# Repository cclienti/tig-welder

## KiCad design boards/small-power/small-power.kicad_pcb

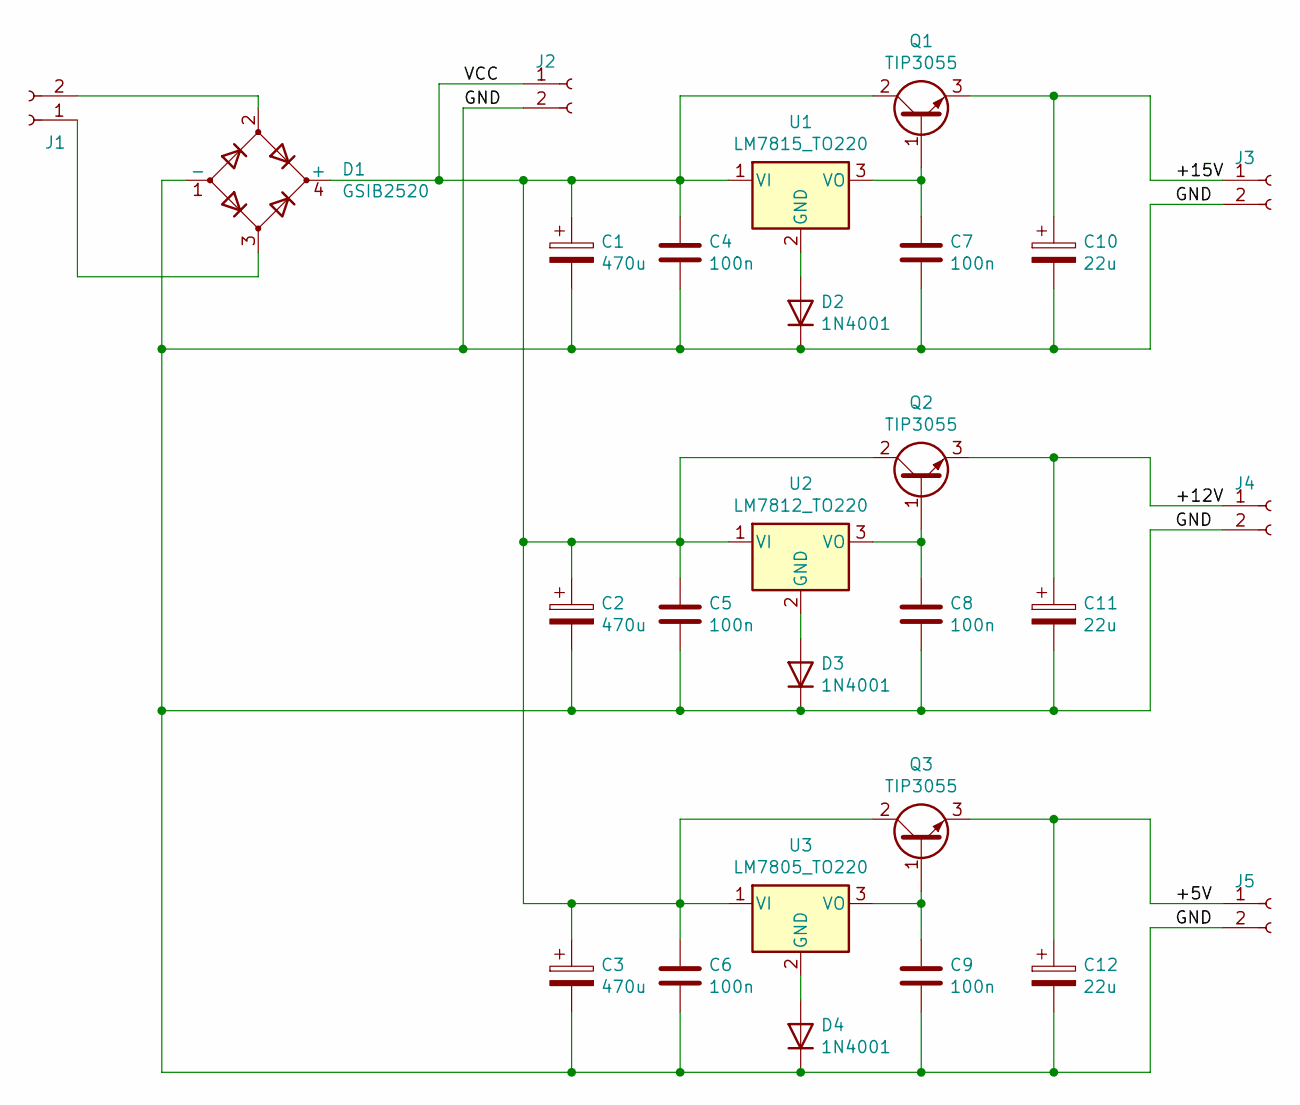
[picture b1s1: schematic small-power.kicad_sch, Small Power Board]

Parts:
C1, C2, C3: 470u; CP_Radial_D13.0mm_P5.00mm
C4, C5, C6, C7, C8, C9: 100n; C_Rect_L4.6mm_W2.0mm_P2.50mm_MKS02_FKP02
C10, C11, C12: 22u; CP_Radial_D5.0mm_P2.50mm
D1: GSIB2520; Diode_Bridge_32.0x5.6x17.0mm_P10.0mm_P7.5mm
D2, D3, D4: 1N4001; D_DO-41_SOD81_P10.16mm_Horizontal
J1, J2, J3, J4, J5: Conn_01x02_Female; PhoenixContact_MSTBVA_2,5_2-G-5,08_1x02_P5.08mm_Vertical
Q1, Q2, Q3: TIP3055; TO-218-3_Vertical
U1: LM7815_TO220; TO-220-3_Vertical
U2: LM7812_TO220; TO-220-3_Vertical
U3: LM7805_TO220; TO-220-3_Vertical

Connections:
/+5V: C12.1, J5.1, Q3.3 (E)
/+12V: C11.1, J4.1, Q2.3 (E)
/+15V: C10.1, J3.1, Q1.3 (E)
/GND: C1.2, C2.2, C3.2, C4.2, C5.2, C6.2, C7.2, C8.2, C9.2, C10.2, C11.2, C12.2, D1.1 (-), D2.1 (K), D3.1 (K), D4.1 (K), J2.2, J3.2, J4.2, J5.2
/VCC: C1.1, C2.1, C3.1, C4.1, C5.1, C6.1, D1.4 (+), J2.1, Q1.2 (C), Q2.2 (C), Q3.2 (C), U1.1 (VI), U2.1 (VI), U3.1 (VI)
unnamed: C7.1, Q1.1 (B), U1.3 (VO)
unnamed: C8.1, Q2.1 (B), U2.3 (VO)
unnamed: C9.1, Q3.1 (B), U3.3 (VO)
unnamed: D1.2, J1.2
unnamed: D1.3, J1.1
unnamed: D2.2 (A), U1.2 (GND)
unnamed: D3.2 (A), U2.2 (GND)
unnamed: D4.2 (A), U3.2 (GND)

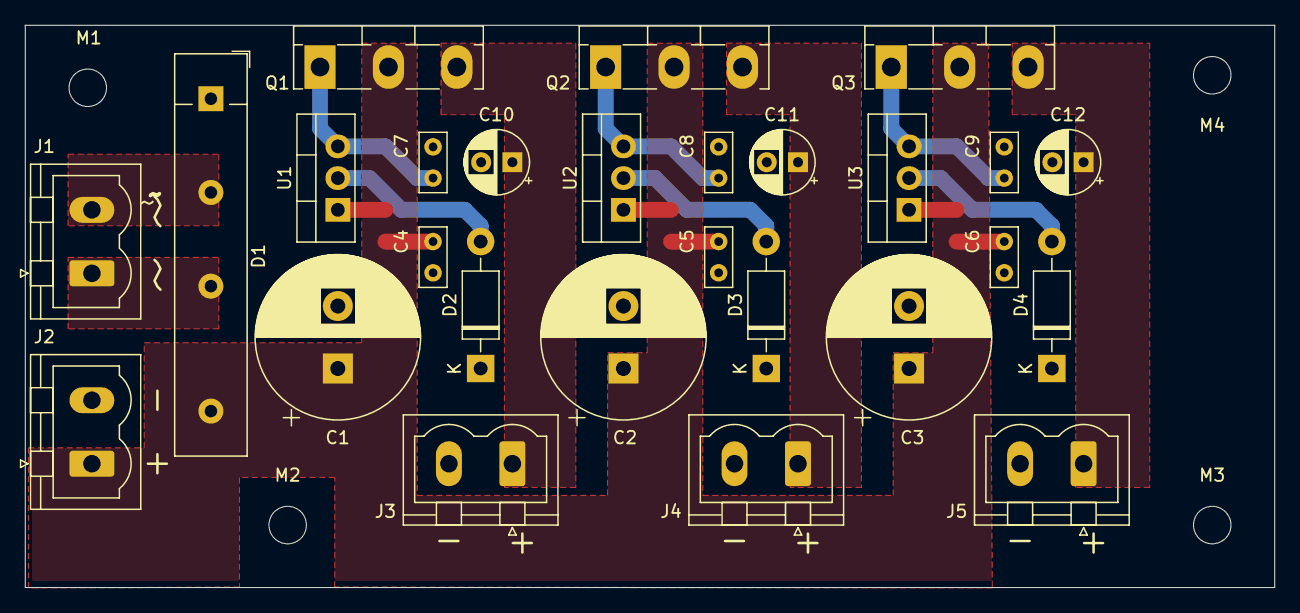
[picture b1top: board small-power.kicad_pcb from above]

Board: 2 copper layers, 100.0 x 45.0 mm, 31 parts (0 on the bottom side), 13 nets.

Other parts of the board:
M1, M2, M3, M4: MountingHole_3mm

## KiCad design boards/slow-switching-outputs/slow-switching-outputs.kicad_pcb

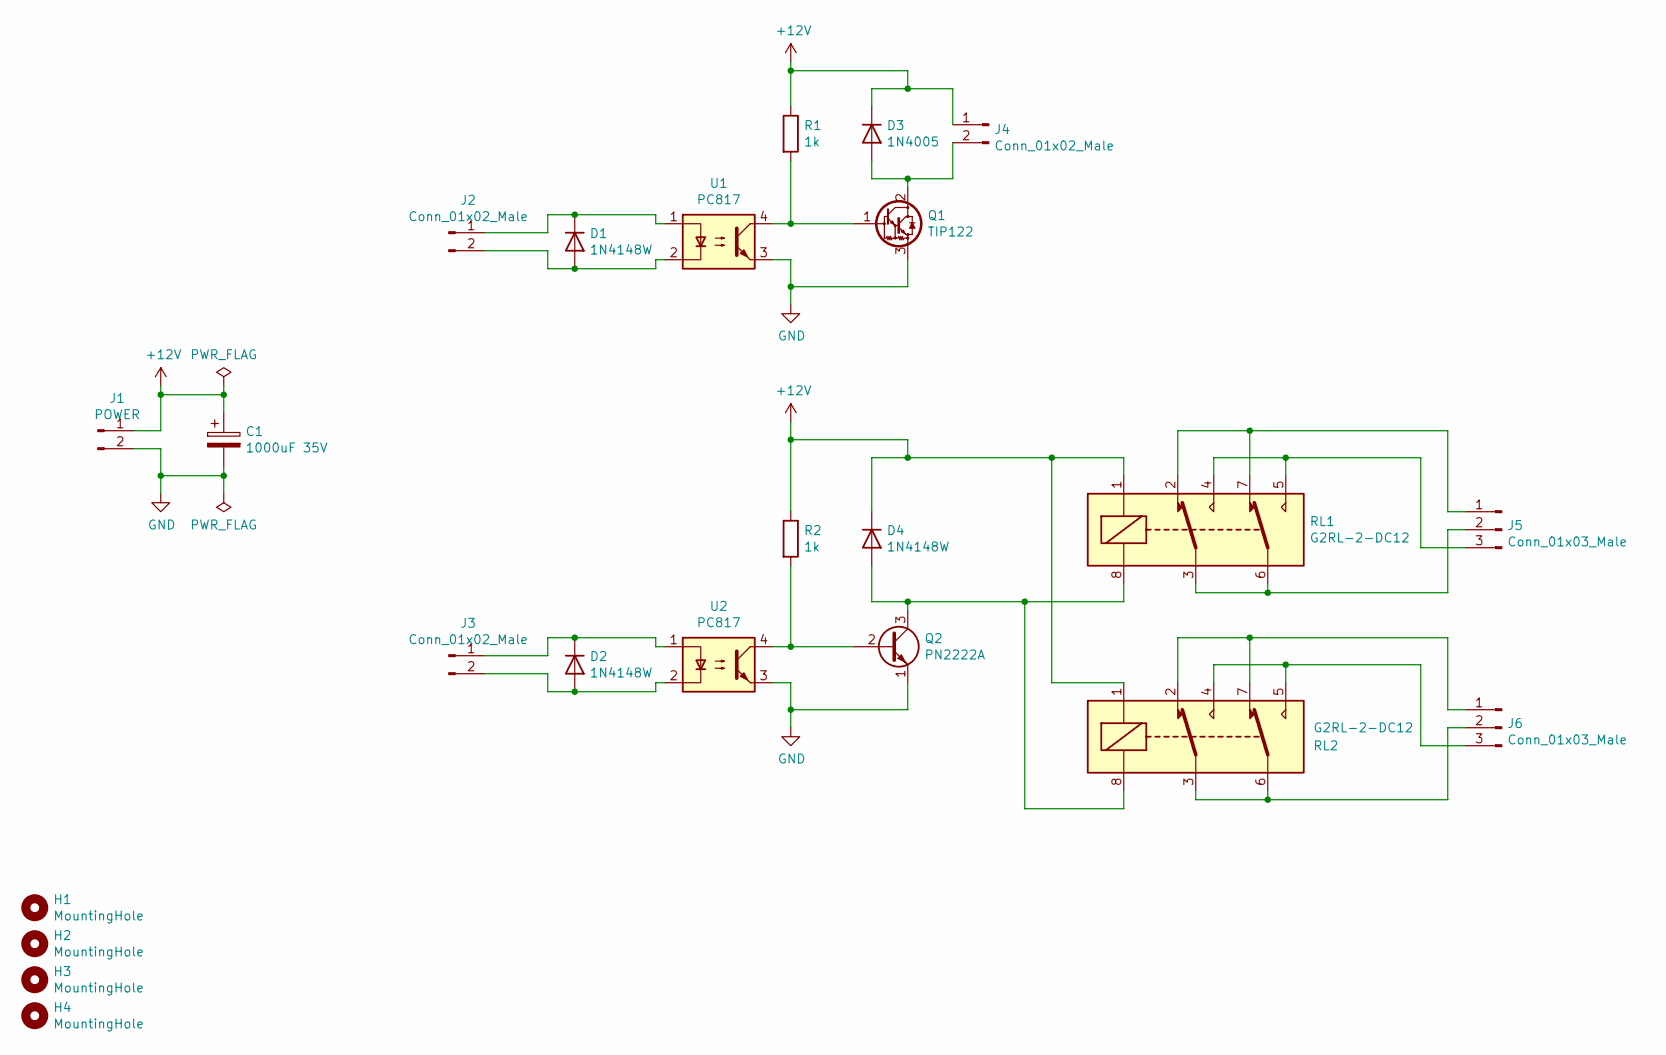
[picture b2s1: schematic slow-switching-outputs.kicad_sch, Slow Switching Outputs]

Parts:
C1: 1000uF 35V; CP_Radial_D16.0mm_P7.50mm
D1, D2, D4: 1N4148W; D_SOD-123
D3: 1N4005; D_SMB_Handsoldering
H1, H2, H3, H4: MountingHole; MountingHole_3.2mm_M3_Pad
J1: POWER; PhoenixContact_MSTBVA_2,5_2-G-5,08_1x02_P5.08mm_Vertical
J2, J3: Conn_01x02_Male; PinHeader_1x02_P2.54mm_Vertical
J4: Conn_01x02_Male; PhoenixContact_MSTBVA_2,5_2-G-5,08_1x02_P5.08mm_Vertical
J5, J6: Conn_01x03_Male; PhoenixContact_MSTBVA_2,5_3-G-5,08_1x03_P5.08mm_Vertical
Q1: TIP122; TO-220-3_Vertical
Q2: PN2222A; TO-18-3
R1, R2: 1k; R_1206_3216Metric_Pad1.30x1.75mm_HandSolder
RL1, RL2: G2RL-2-DC12; Relay_DPDT_Omron_G2RL
U1, U2: PC817; DIP-4_W7.62mm

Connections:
+12V: C1.1, D3.1 (K), D4.1 (K), J1.1, J4.1, R1.1, R2.1, RL1.1, RL2.1
GND: C1.2, J1.2, Q1.3 (E), Q2.1 (E), U1.3, U2.3
unnamed: D1.1 (K), J2.1, U1.1
unnamed: D1.2 (A), J2.2, U1.2
unnamed: D2.1 (K), J3.1, U2.1
unnamed: D2.2 (A), J3.2, U2.2
unnamed: D3.2 (A), J4.2, Q1.2 (C)
unnamed: D4.2 (A), Q2.3 (C), RL1.8, RL2.8
unnamed: J5.1, RL1.2, RL1.7
unnamed: J5.2, RL1.3, RL1.6
unnamed: J5.3, RL1.4, RL1.5
unnamed: J6.1, RL2.2, RL2.7
unnamed: J6.2, RL2.3, RL2.6
unnamed: J6.3, RL2.4, RL2.5
unnamed: Q1.1 (B), R1.2, U1.4
unnamed: Q2.2 (B), R2.2, U2.4

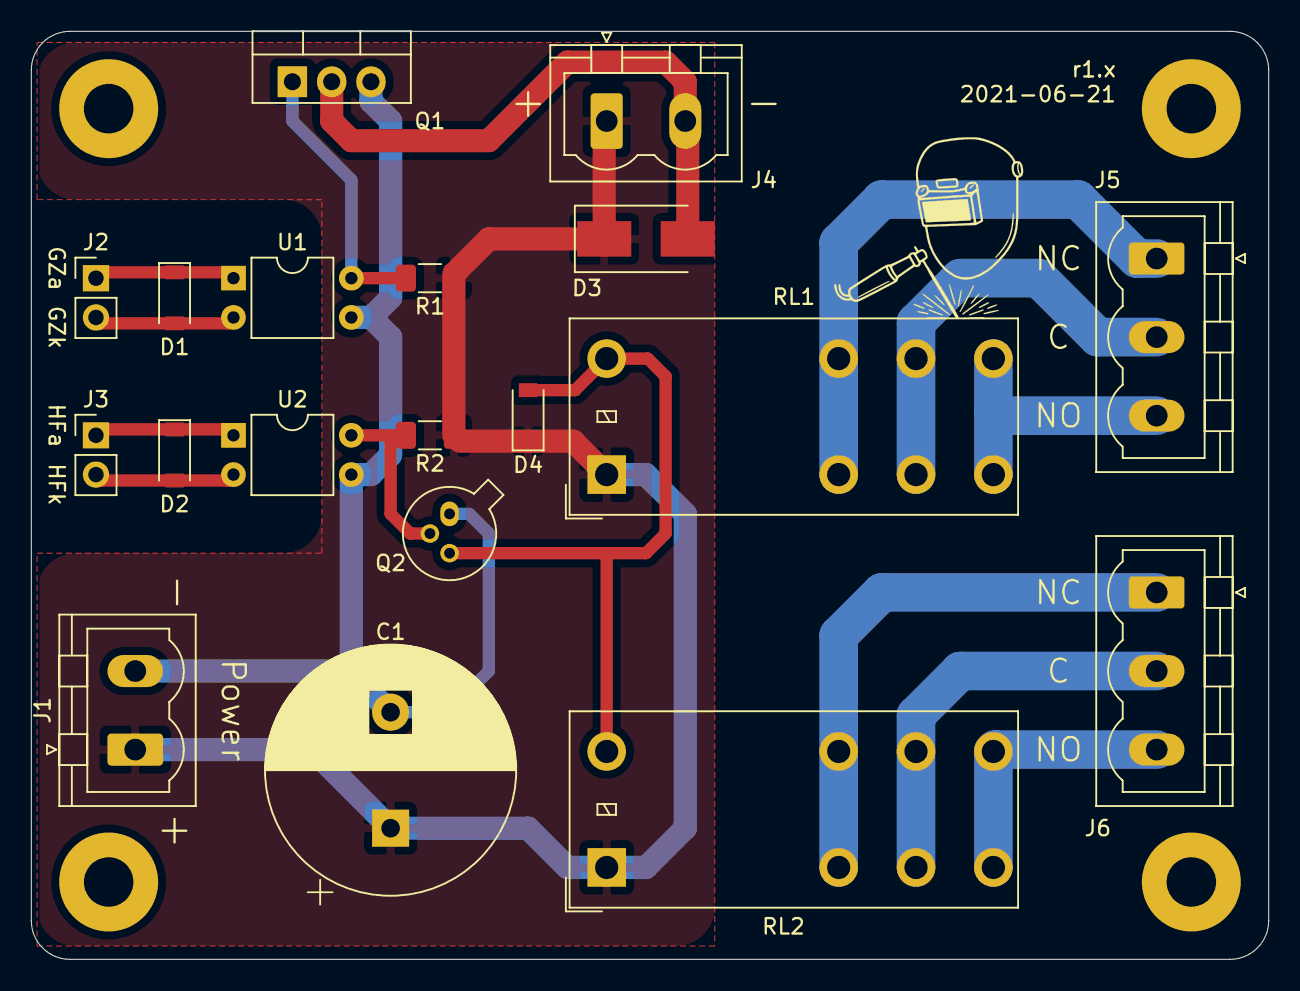
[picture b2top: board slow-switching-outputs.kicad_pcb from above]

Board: 2 copper layers, 80.0 x 60.0 mm, 23 parts (0 on the bottom side), 16 nets.

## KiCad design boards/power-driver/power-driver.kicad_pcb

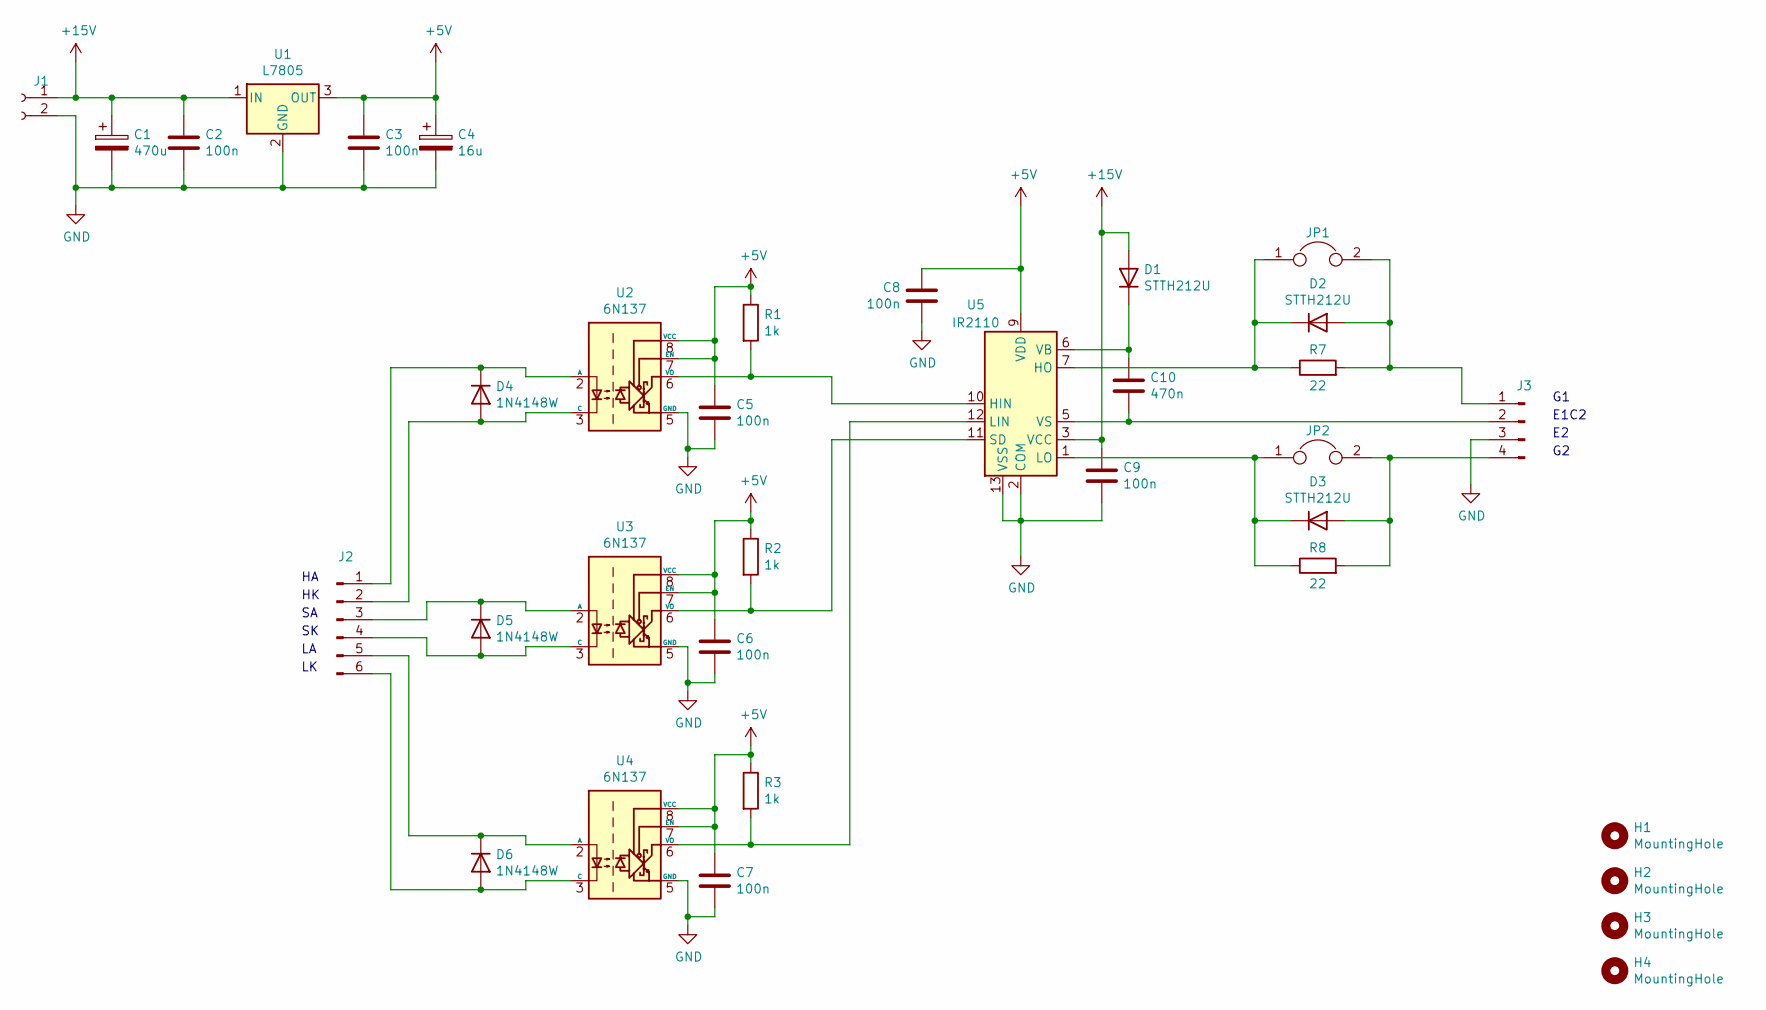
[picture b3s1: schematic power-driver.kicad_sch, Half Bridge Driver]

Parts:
C1: 470u; CP_Elec_6.3x7.7
C2, C3, C5, C6, C7, C8, C9: 100n; C_1206_3216Metric_Pad1.33x1.80mm_HandSolder
C4: 16u; CP_Elec_5x5.3
C10: 470n; C_Rect_L13.0mm_W6.0mm_P10.00mm_FKS3_FKP3_MKS4
D1, D2, D3: STTH212U; D_SMB
D4, D5, D6: 1N4148W; D_SOD-123
H1, H2, H3, H4: MountingHole; MountingHole_3.2mm_M3_Pad
J1: Conn_01x02_Female; PhoenixContact_MSTBVA_2,5_2-G-5,08_1x02_P5.08mm_Vertical
J2: Conn_01x06_Male; PinHeader_1x06_P2.54mm_Vertical
J3: Conn_01x04_Male; PinHeader_1x04_P2.54mm_Vertical
JP1, JP2: Jumper; PinHeader_1x02_P2.54mm_Vertical
R1, R2, R3: 1k; R_1206_3216Metric_Pad1.30x1.75mm_HandSolder
R7, R8: 22; R_1206_3216Metric_Pad1.30x1.75mm_HandSolder
U1: L7805; TO-220-3_Horizontal_TabDown
U2, U3, U4: 6N137; DIP-8_W7.62mm
U5: IR2110; DIP-14_W7.62mm

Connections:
+5V: C3.1, C4.1, C5.1, C6.1, C7.1, C8.2, R1.1, R2.1, R3.1, U1.3 (OUT), U2.7 (EN), U2.8 (VCC), U3.7 (EN), U3.8 (VCC), U4.7 (EN), U4.8 (VCC), U5.9 (VDD)
+15V: C1.1, C2.1, C9.1, D1.2 (A), J1.1, U1.1 (IN), U5.3 (VCC)
GND: C1.2, C2.2, C3.2, C4.2, C5.2, C6.2, C7.2, C8.1, C9.2, J1.2, J3.3, U1.2 (GND), U2.5 (GND), U3.5 (GND), U4.5 (GND), U5.2 (COM), U5.13 (VSS)
unnamed: C10.1, D1.1 (K), U5.6 (VB)
unnamed: C10.2, J3.2, U5.5 (VS)
unnamed: D2.1 (K), JP1.1, R7.1, U5.7 (HO)
unnamed: D2.2 (A), J3.1, JP1.2, R7.2
unnamed: D3.1 (K), JP2.1, R8.1, U5.1 (LO)
unnamed: D3.2 (A), J3.4, JP2.2, R8.2
unnamed: D4.1 (K), J2.1, U2.2 (A)
unnamed: D4.2 (A), J2.2, U2.3 (C)
unnamed: D5.1 (K), J2.3, U3.2 (A)
unnamed: D5.2 (A), J2.4, U3.3 (C)
unnamed: D6.1 (K), J2.5, U4.2 (A)
unnamed: D6.2 (A), J2.6, U4.3 (C)
unnamed: R1.2, U2.6 (VO), U5.10 (HIN)
unnamed: R2.2, U3.6 (VO), U5.11 (SD)
unnamed: R3.2, U4.6 (VO), U5.12 (LIN)

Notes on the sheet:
E1C2

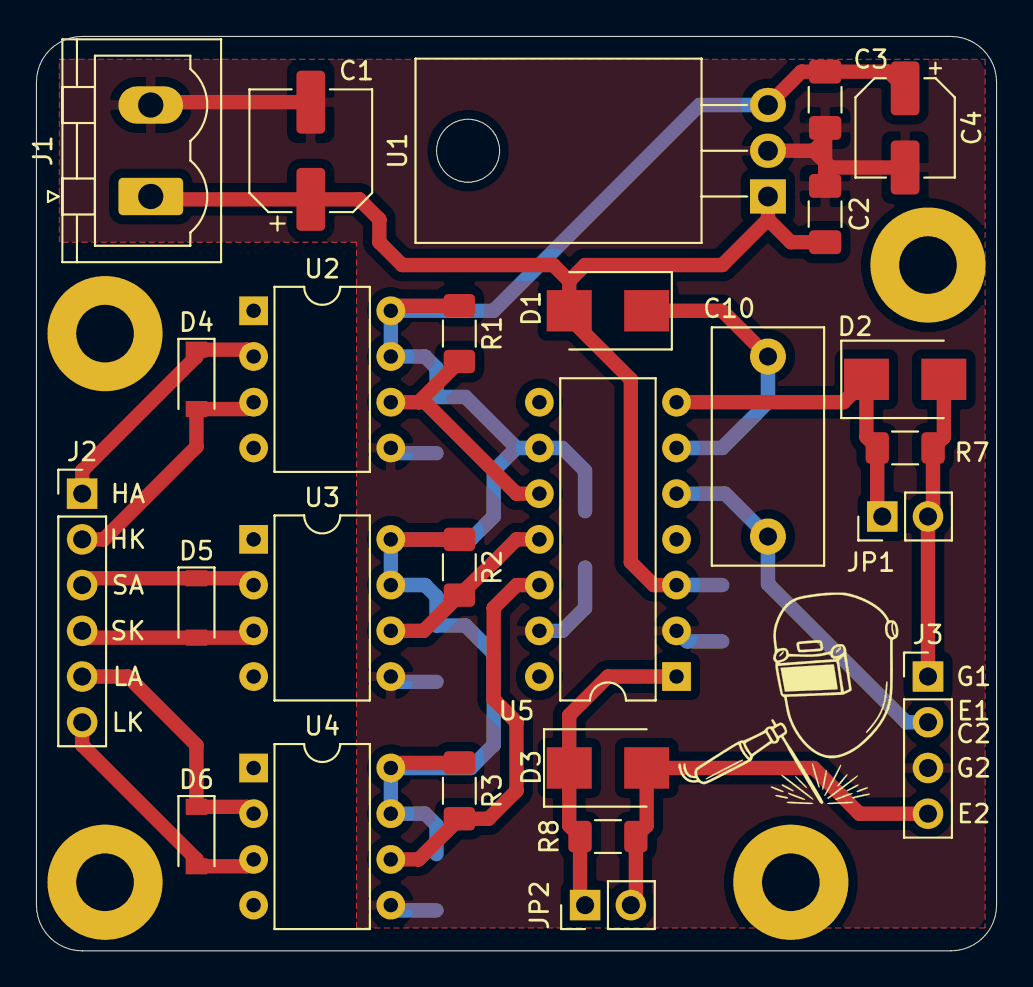
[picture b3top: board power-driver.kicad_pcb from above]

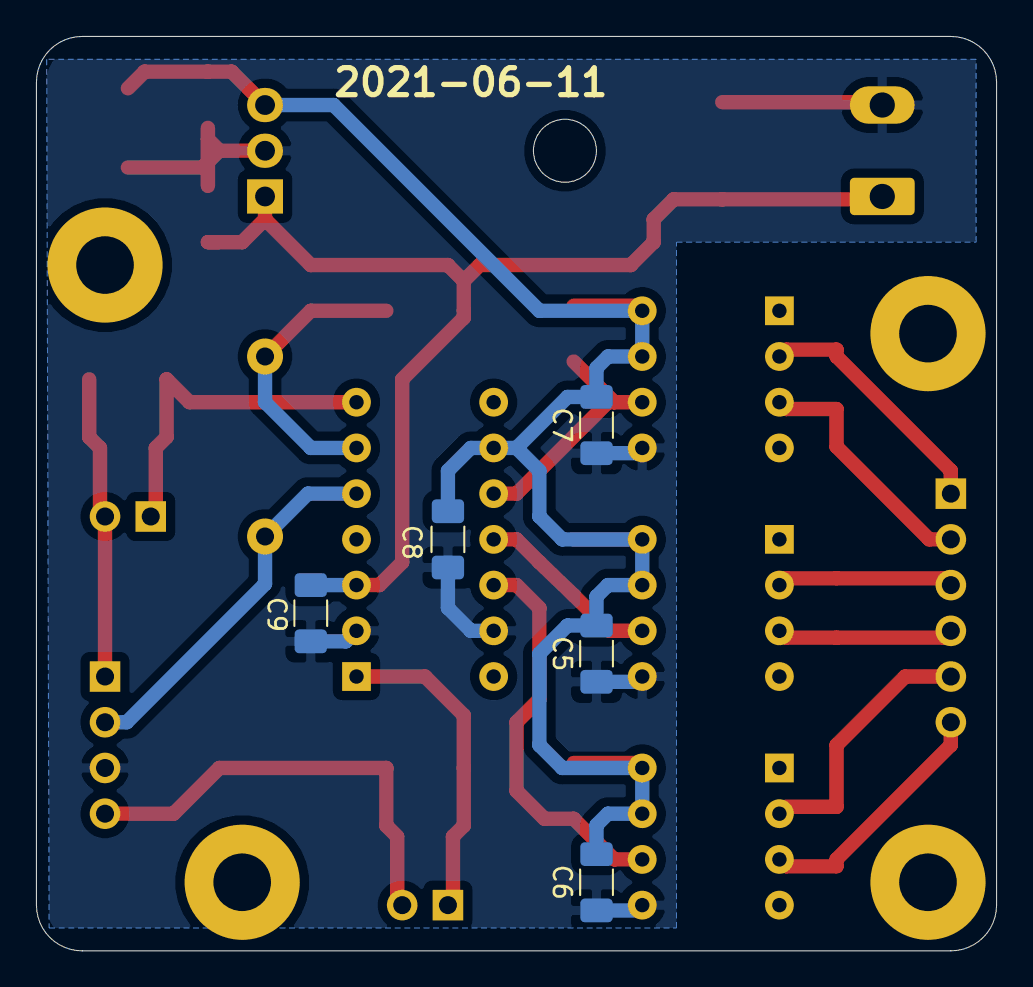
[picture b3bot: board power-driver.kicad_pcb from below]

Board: 2 copper layers, 53.3 x 50.8 mm, 35 parts (5 on the bottom side), 18 nets.

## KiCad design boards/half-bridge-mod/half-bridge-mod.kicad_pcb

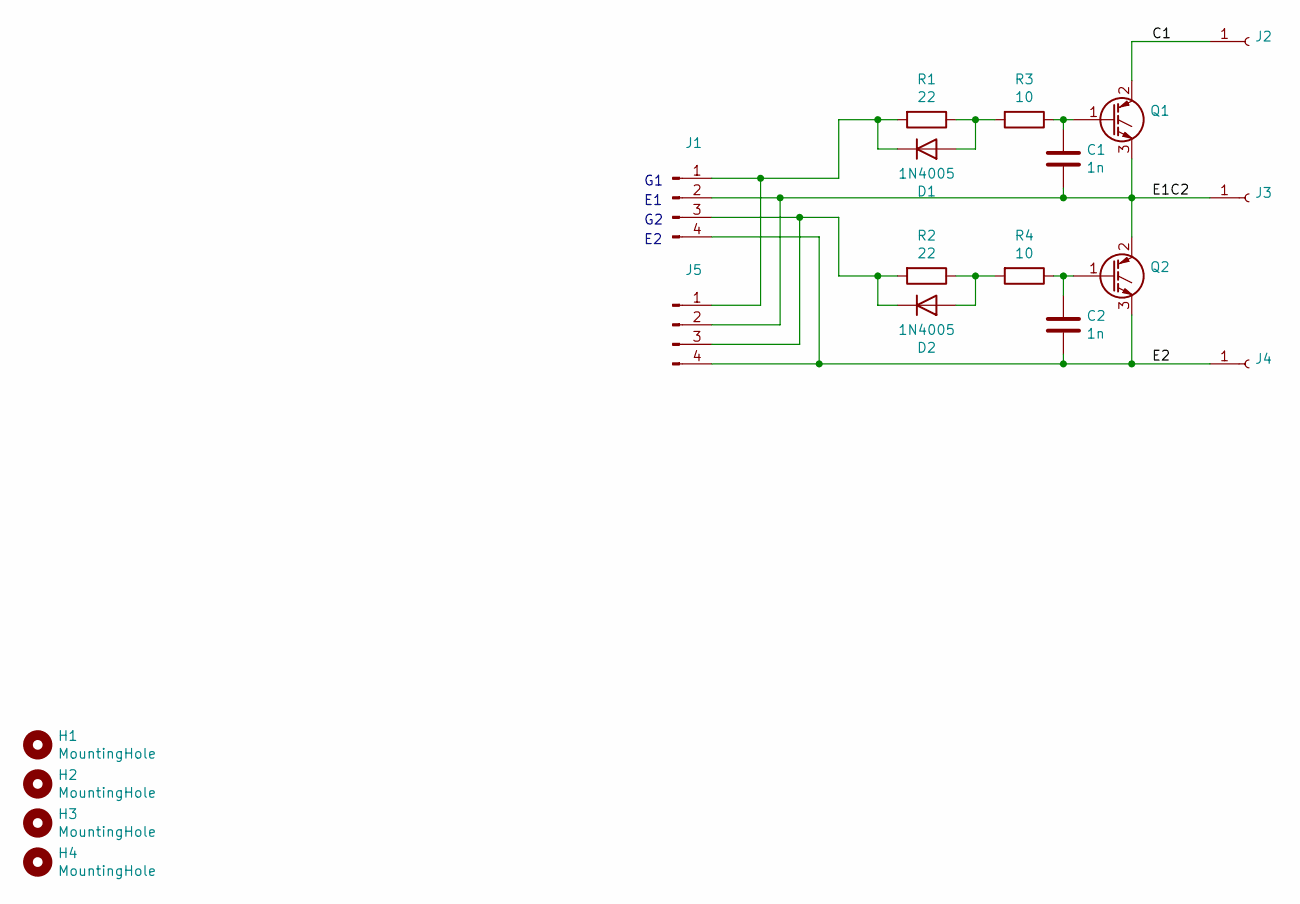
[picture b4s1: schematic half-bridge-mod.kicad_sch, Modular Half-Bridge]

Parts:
C1, C2: 1n; C_1206_3216Metric
D1, D2: 1N4005; D_SMA
H1, H2, H3, H4: MountingHole; MountingHole_2.2mm_M2
J1, J5: Conn_01x04_Male; PinHeader_1x04_P2.54mm_Vertical
J2, J3, J4: Conn_01x01_Female; Terminal_Block_Welder_no_hole
Q1, Q2: Q_NIGBT_GCE; TO-247-3_Horizontal_TabUp
R1, R2: 22; R_1206_3216Metric
R3, R4: 10; R_1206_3216Metric

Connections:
/C1: J2.1, Q1.2 (C)
/E1C2: C1.2, J1.2, J3.1, J5.2, Q1.3 (E), Q2.2 (C)
/E2: C2.2, J1.4, J4.1, J5.4, Q2.3 (E)
unnamed: C1.1, Q1.1 (G), R3.1
unnamed: C2.1, Q2.1 (G), R4.1
unnamed: D1.1 (K), J1.1, J5.1, R1.2
unnamed: D1.2 (A), R1.1, R3.2
unnamed: D2.1 (K), J1.3, J5.3, R2.2
unnamed: D2.2 (A), R2.1, R4.2

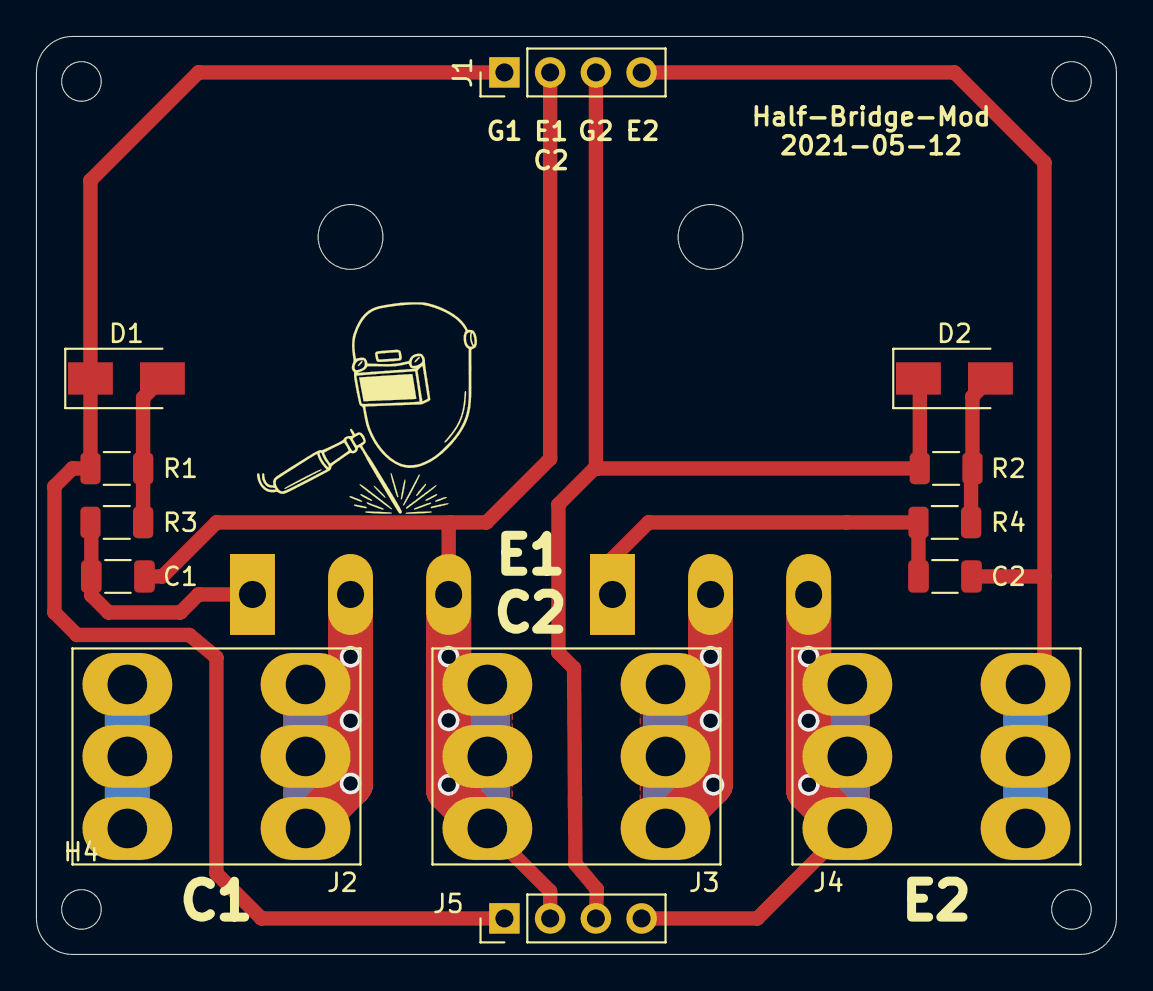
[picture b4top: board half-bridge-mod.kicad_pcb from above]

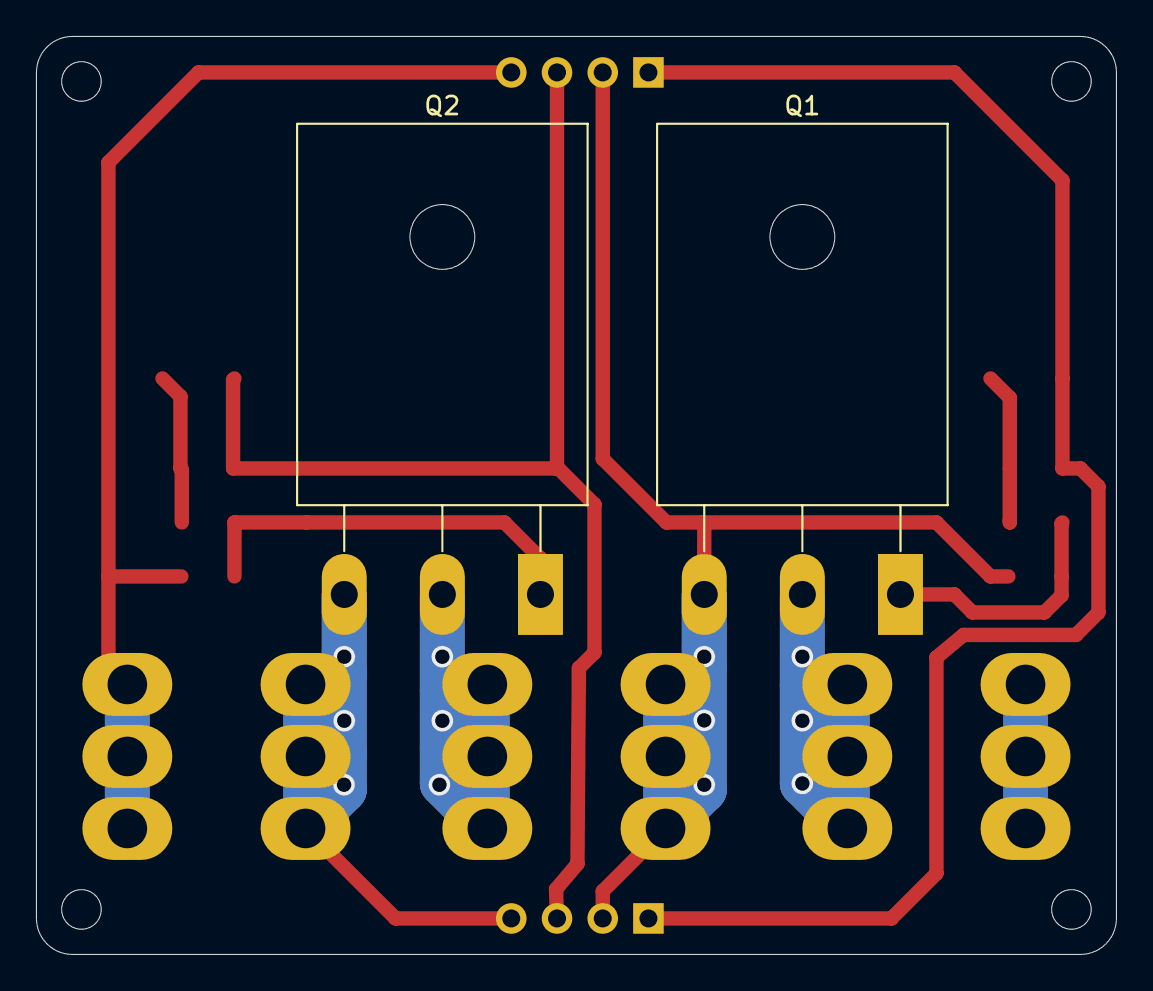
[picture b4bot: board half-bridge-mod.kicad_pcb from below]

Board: 2 copper layers, 60.0 x 51.0 mm, 19 parts (2 on the bottom side), 9 nets.

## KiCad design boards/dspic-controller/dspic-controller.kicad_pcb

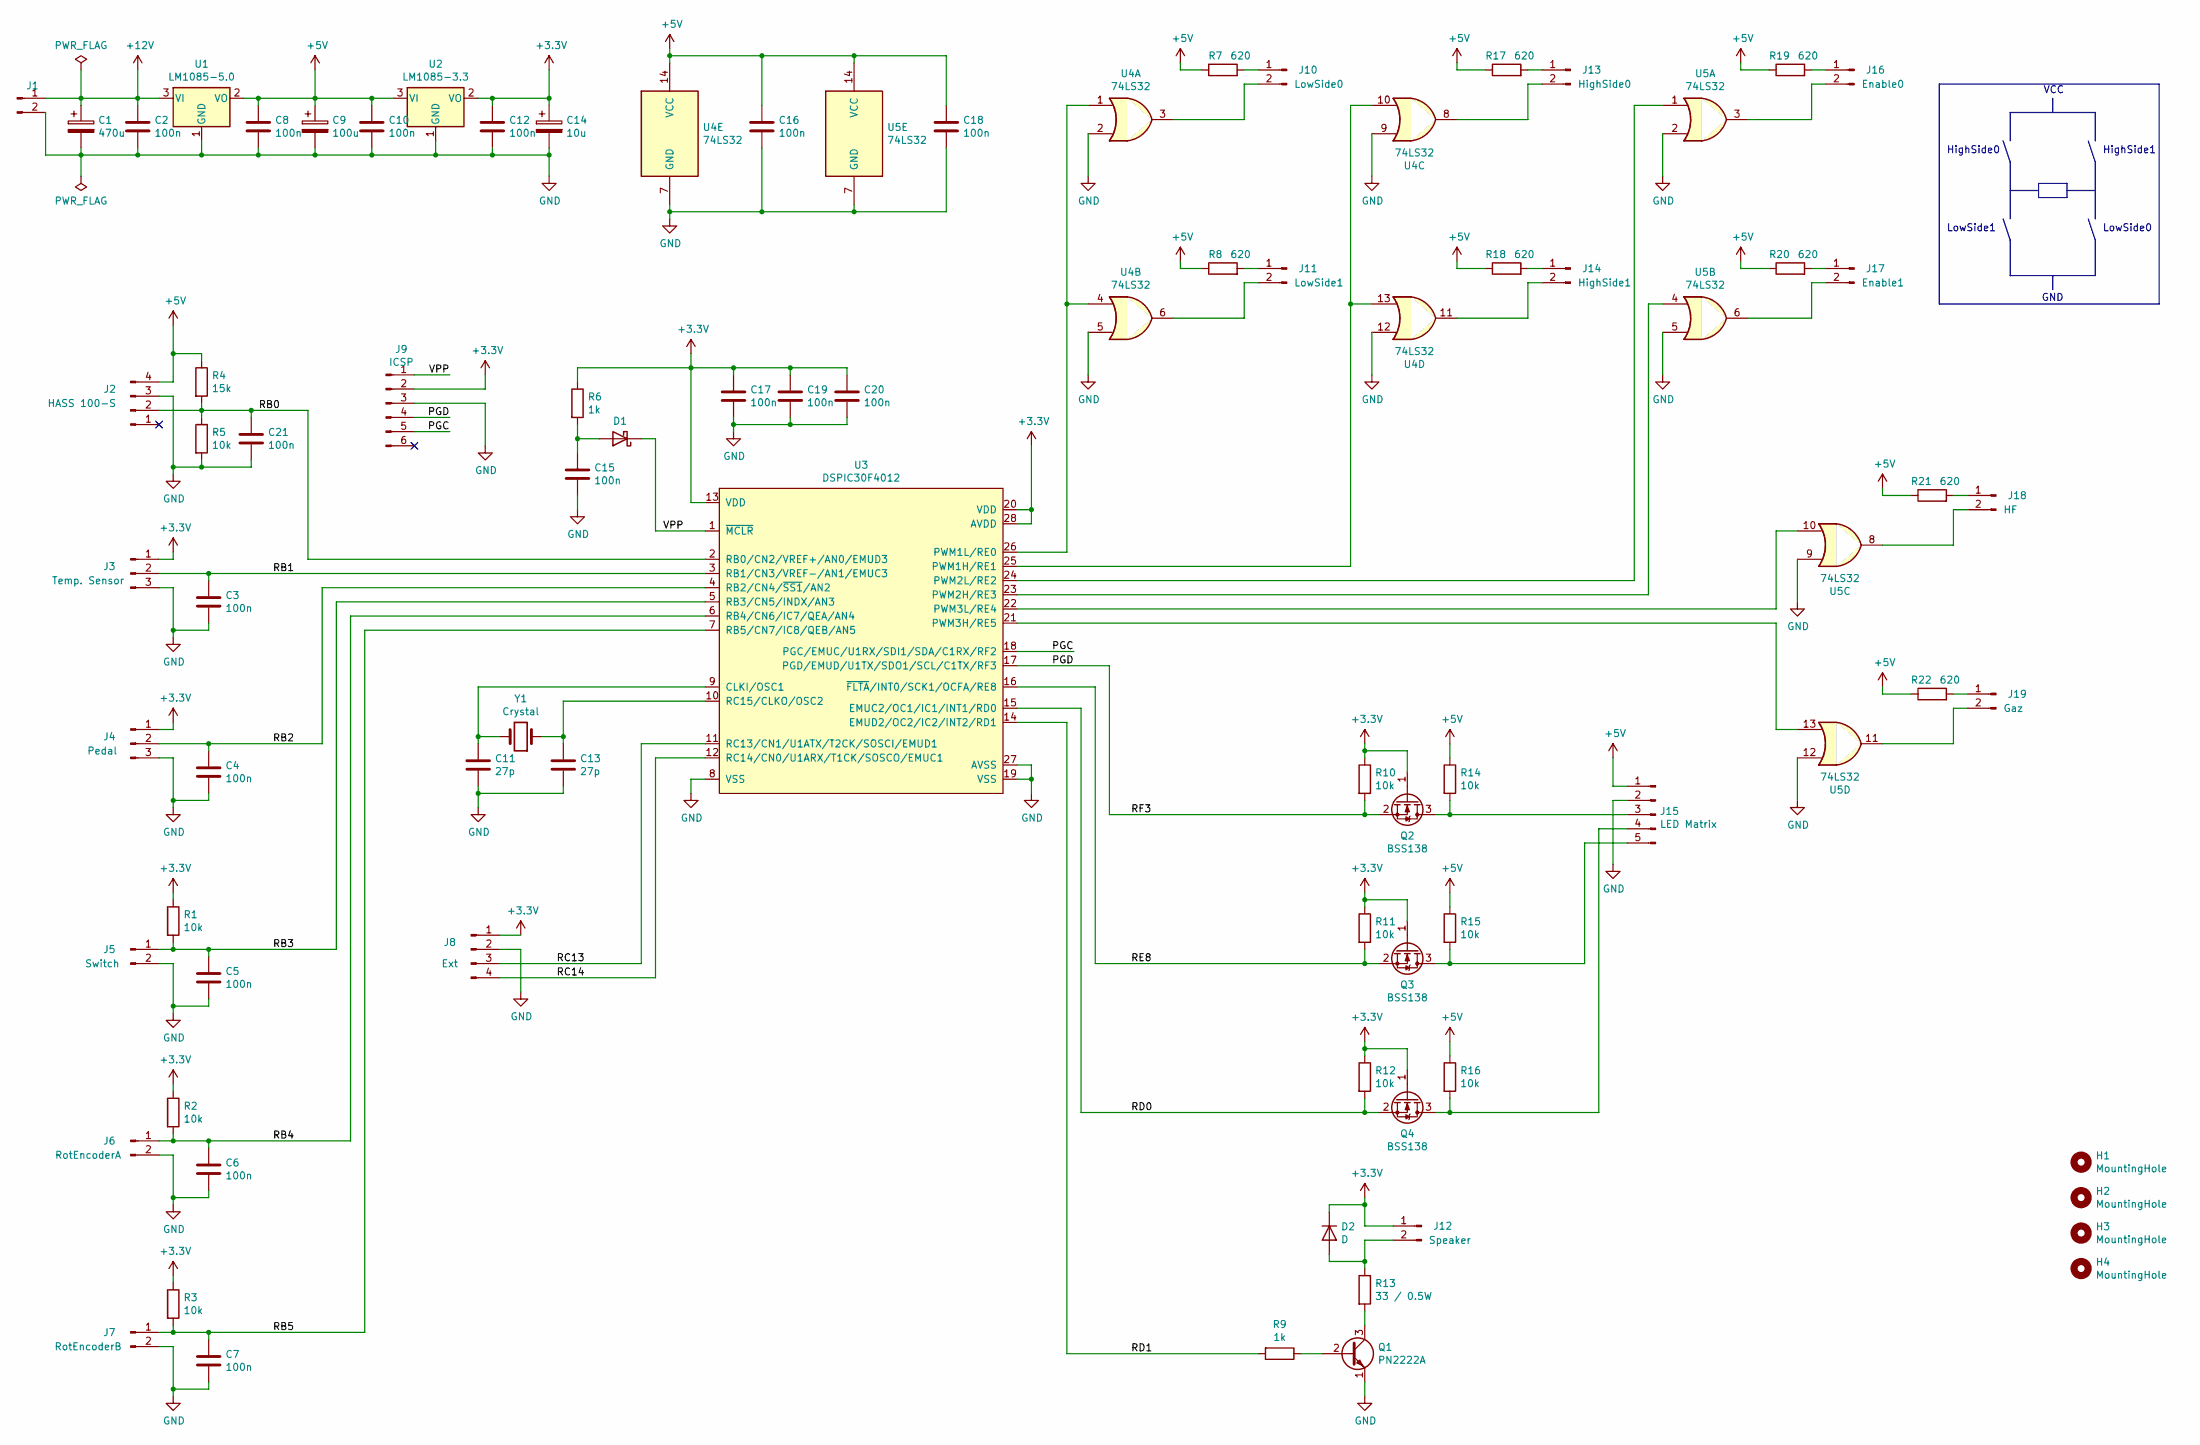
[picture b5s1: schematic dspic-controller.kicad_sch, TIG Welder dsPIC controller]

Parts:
C1: 470u; CP_Radial_D13.0mm_P5.00mm
C2, C3, C4, C5, C6, C7, C8, C10, C12, C15, C16, C17, C18, C19, C20, C21: 100n; C_1206_3216Metric_Pad1.33x1.80mm_HandSolder
C9: 100u; CP_Elec_6.3x5.4
C11, C13: 27p; C_1206_3216Metric_Pad1.33x1.80mm_HandSolder
C14: 10u; CP_Elec_5x5.3
D1: MBR1020VL; D_1206_3216Metric_Pad1.42x1.75mm_HandSolder
D2: D; D_1206_3216Metric_Pad1.42x1.75mm_HandSolder
H1, H2, H3, H4: MountingHole; MountingHole_3.2mm_M3
J1: Power Input; PhoenixContact_MSTBVA_2,5_2-G-5,08_1x02_P5.08mm_Vertical
J2: HASS 100-S; PinHeader_1x04_P2.54mm_Vertical
J3: Temp. Sensor; PinHeader_1x03_P2.54mm_Vertical
J4: Pedal; PinHeader_1x03_P2.54mm_Vertical
J5: Switch; PinHeader_1x02_P2.54mm_Vertical
J6: RotEncoderA; PinHeader_1x02_P2.54mm_Vertical
J7: RotEncoderB; PinHeader_1x02_P2.54mm_Vertical
J8: Ext; PinHeader_1x04_P2.54mm_Vertical
J9: ICSP; PinHeader_1x06_P2.54mm_Vertical
J10: LowSide0; PinHeader_1x02_P2.54mm_Vertical
J11: LowSide1; PinHeader_1x02_P2.54mm_Vertical
J12: Speaker; PinHeader_1x02_P2.54mm_Vertical
J13: HighSide0; PinHeader_1x02_P2.54mm_Vertical
J14: HighSide1; PinHeader_1x02_P2.54mm_Vertical
J15: LED Matrix; PinHeader_1x05_P2.54mm_Vertical
J16: Enable0; PinHeader_1x02_P2.54mm_Vertical
J17: Enable1; PinHeader_1x02_P2.54mm_Vertical
J18: HF; PinHeader_1x02_P2.54mm_Vertical
J19: Gaz; PinHeader_1x02_P2.54mm_Vertical
Q1: PN2222A; TO-18-3
Q2, Q3, Q4: BSS138; SOT-23_Handsoldering
R1, R2, R3, R5, R10, R11, R12, R14, R15, R16: 10k; R_1206_3216Metric_Pad1.30x1.75mm_HandSolder
R4: 15k; R_1206_3216Metric_Pad1.30x1.75mm_HandSolder
R6, R9: 1k; R_1206_3216Metric_Pad1.30x1.75mm_HandSolder
R7, R8, R17, R18, R19, R20, R21, R22: 620; R_1206_3216Metric_Pad1.30x1.75mm_HandSolder
R13: 33 / 0.5W; R_Axial_DIN0207_L6.3mm_D2.5mm_P7.62mm_Horizontal
U1: LM1085-5.0; TO-220-3_Vertical
U2: LM1085-3.3; TO-220-3_Vertical
U3: DSPIC30F4012; DIP-28_W7.62mm
U4, U5: 74LS32; DIP-14_W7.62mm
Y1: Crystal; Crystal_SMD_HC49-SD

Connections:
+3V3: C12.1, C14.1, C17.1, C19.1, C20.1, D2.1 (K), J3.1, J4.1, J8.1, J9.2, J12.1, Q2.1 (G), Q3.1 (G), Q4.1 (G), R1.1, R2.1, R3.1, R6.1, R10.1, R11.1, R12.1, U2.2 (VO), U3.13 (VDD), U3.20 (VDD), U3.28 (AVDD)
+5V: C8.1, C9.1, C10.1, C16.1, C18.1, J2.4, J15.1, R4.1, R7.1, R8.1, R14.1, R15.1, R16.1, R17.1, R18.1, R19.1, R20.1, R21.1, R22.1, U1.2 (VO), U2.3 (VI), U4.14 (VCC), U5.14 (VCC)
+12V: C1.1, C2.1, J1.1, U1.3 (VI)
/PGC: J9.5, U3.18 (PGC/EMUC/U1RX/SDI1/SDA/C1RX/RF2)
/PGD: J9.4, Q2.2 (S), R10.2, U3.17 (PGD/EMUD/U1TX/SDO1/SCL/C1TX/RF3)
/RB0: C21.1, J2.2, R4.2, R5.1, U3.2 (RB0/CN2/VREF+/AN0/EMUD3)
/RB1: C3.1, J3.2, U3.3 (RB1/CN3/VREF-/AN1/EMUC3)
/RB2: C4.1, J4.2, U3.4 (RB2/CN4/~SS1/AN2)
/RB3: C5.1, J5.1, R1.2, U3.5 (RB3/CN5/INDX/AN3)
/RB4: C6.1, J6.1, R2.2, U3.6 (RB4/CN6/IC7/QEA/AN4)
/RB5: C7.1, J7.1, R3.2, U3.7 (RB5/CN7/IC8/QEB/AN5)
/RC13: J8.3, U3.11 (RC13/CN1/U1ATX/T2CK/SOSCI/EMUD1)
/RC14: J8.4, U3.12 (RC14/CN0/U1ARX/T1CK/SOSCO/EMUC1)
/RD0: Q4.2 (S), R12.2, U3.15 (EMUC2/OC1/IC1/INT1/RD0)
/RD1: R9.2, U3.14 (EMUD2/OC2/IC2/INT2/RD1)
/RE8: Q3.2 (S), R11.2, U3.16 (~FLTA/INT0/SCK1/OCFA/RE8)
/VPP: D1.1 (K), J9.1, U3.1 (~MCLR)
GND: C1.2, C2.2, C3.2, C4.2, C5.2, C6.2, C7.2, C8.2, C9.2, C10.2, C11.2, C12.2, C13.2, C14.2, C15.2, C16.2, C17.2, C18.2, C19.2, C20.2, C21.2, J1.2, J2.3, J3.3, J4.3, J5.2, J6.2, J7.2, J8.2, J9.3, J15.2, Q1.1 (E), R5.2, U1.1 (GND), U2.1 (GND), U3.8 (VSS), U3.19 (VSS), U3.27 (AVSS), U4.2, U4.5, U4.7 (GND), U4.9, U4.12, U5.2, U5.5, U5.7 (GND), U5.9, U5.12
unnamed: C11.1, U3.9 (CLKI/OSC1), Y1.2
unnamed: C13.1, U3.10 (RC15/CLKO/OSC2), Y1.1
unnamed: C15.1, D1.2 (A), R6.2
unnamed: D2.2 (A), J12.2, R13.1
unnamed: J10.1, R7.2
unnamed: J10.2, U4.3
unnamed: J11.1, R8.2
unnamed: J11.2, U4.6
unnamed: J13.1, R17.2
unnamed: J13.2, U4.8
unnamed: J14.1, R18.2
unnamed: J14.2, U4.11
unnamed: J15.3, Q2.3 (D), R14.2
unnamed: J15.4, Q4.3 (D), R16.2
unnamed: J15.5, Q3.3 (D), R15.2
unnamed: J16.1, R19.2
unnamed: J16.2, U5.3
unnamed: J17.1, R20.2
unnamed: J17.2, U5.6
unnamed: J18.1, R21.2
unnamed: J18.2, U5.8
unnamed: J19.1, R22.2
unnamed: J19.2, U5.11
unnamed: Q1.2 (B), R9.1
unnamed: Q1.3 (C), R13.2
unnamed: U3.21 (PWM3H/RE5), U5.13
unnamed: U3.22 (PWM3L/RE4), U5.10
unnamed: U3.23 (PWM2H/RE3), U5.4
unnamed: U3.24 (PWM2L/RE2), U5.1
unnamed: U3.25 (PWM1H/RE1), U4.10, U4.13
unnamed: U3.26 (PWM1L/RE0), U4.1, U4.4

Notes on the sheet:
HighSide0
LowSide0
LowSide1
HighSide1
VCC
GND
